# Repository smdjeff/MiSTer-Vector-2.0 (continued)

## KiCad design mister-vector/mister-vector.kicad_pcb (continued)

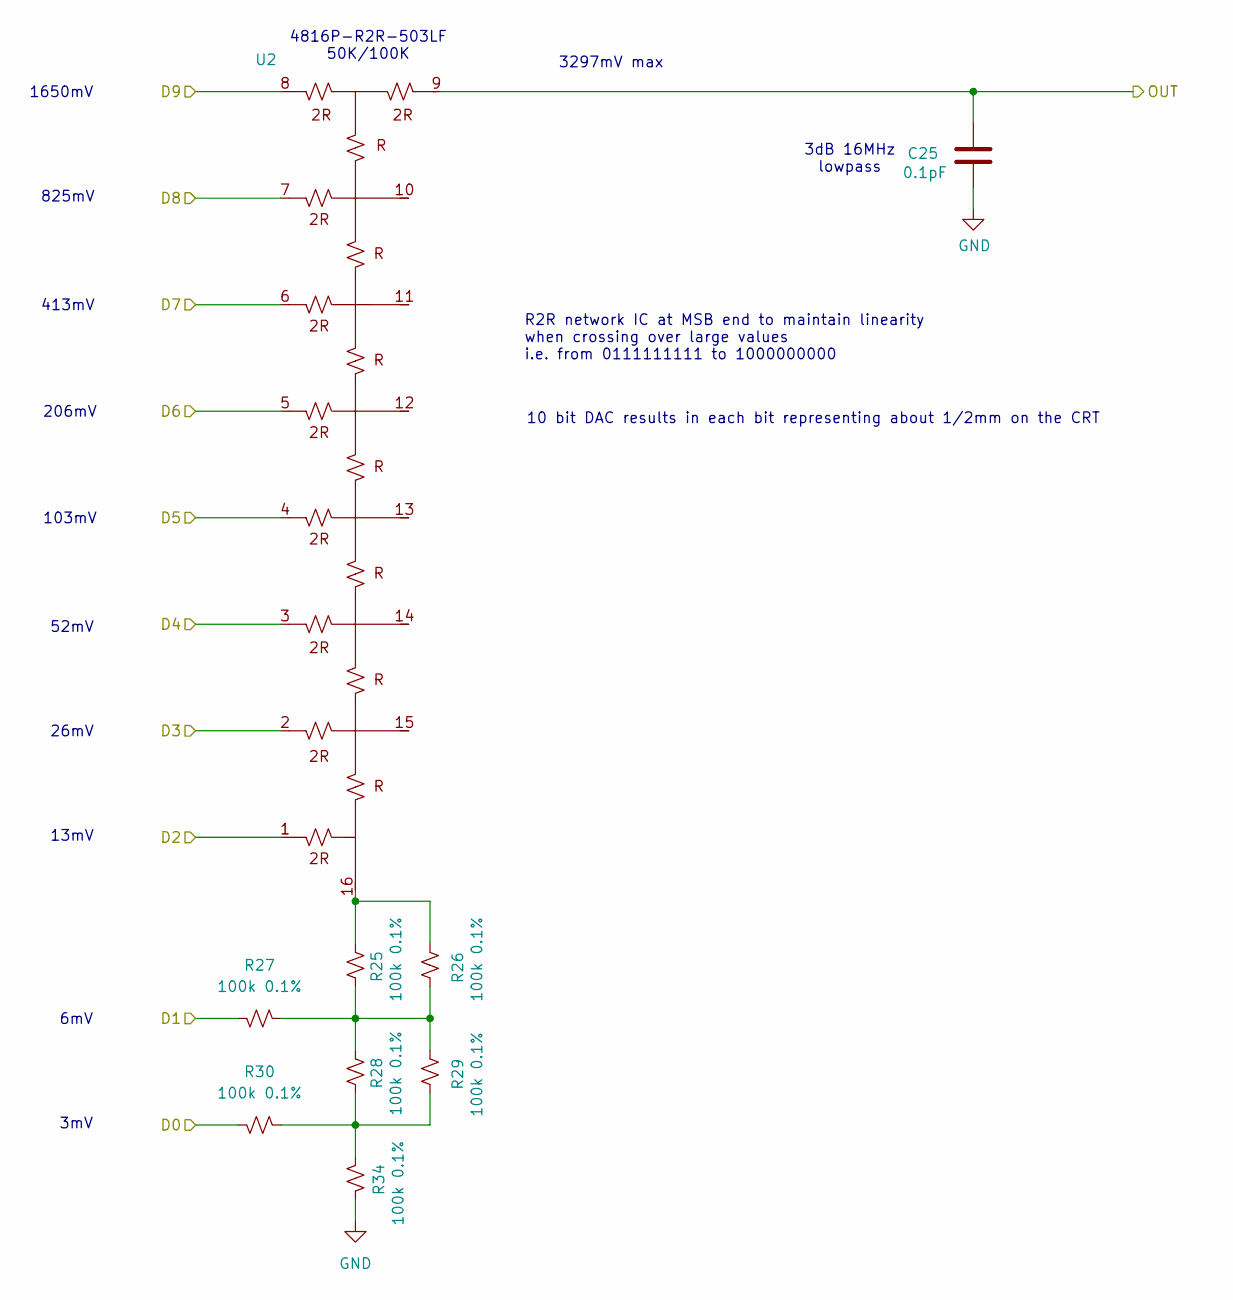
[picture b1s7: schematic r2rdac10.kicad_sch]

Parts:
C25: 0.1pF; C_0402_1005Metric; LCSC C5448807
R25, R26, R27, R28, R29, R30, R34: 100k 0.1%; R_0402_1005Metric; LCSC C852472
U2: 4816P-R2R-503LF; SOIC-16W_5.3x10.2mm_P1.27mm; LCSC C1518174

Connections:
/Vector Amplifiers/DAC_X: C25.2, U2.9; also elsewhere on the board
/Vector DACs/R2R_DAC_X/D0: R30.2; also elsewhere on the board
/Vector DACs/R2R_DAC_X/D1: R27.2; also elsewhere on the board
/Vector DACs/R2R_DAC_X/D2: U2.1; also elsewhere on the board
/Vector DACs/R2R_DAC_X/D3: U2.2; also elsewhere on the board
/Vector DACs/R2R_DAC_X/D4: U2.3; also elsewhere on the board
/Vector DACs/R2R_DAC_X/D5: U2.4; also elsewhere on the board
/Vector DACs/R2R_DAC_X/D6: U2.5; also elsewhere on the board
/Vector DACs/R2R_DAC_X/D7: U2.6; also elsewhere on the board
/Vector DACs/R2R_DAC_X/D8: U2.7; also elsewhere on the board
/Vector DACs/R2R_DAC_X/D9: U2.8; also elsewhere on the board
GND: C25.1, R34.2; also elsewhere on the board
unnamed: R25.1, R26.1, U2.16
unnamed: R25.2, R26.2, R27.1, R28.1, R29.1
unnamed: R28.2, R29.2, R30.1, R34.1

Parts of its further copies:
C26: 0.1pF; C_0402_1005Metric; LCSC C5448807
R35, R36, R37, R38, R39, R40, R44: 100k 0.1%; R_0402_1005Metric; LCSC C852472
U3: 4816P-R2R-503LF; SOIC-16W_5.3x10.2mm_P1.27mm; LCSC C1518174

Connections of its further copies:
/Vector Amplifiers/DAC_Y: C26.2, U3.9; also elsewhere on the board
/Vector DACs/R2R_DAC_Y/D0: R40.2; also elsewhere on the board
/Vector DACs/R2R_DAC_Y/D1: R37.2; also elsewhere on the board
/Vector DACs/R2R_DAC_Y/D2: U3.1; also elsewhere on the board
/Vector DACs/R2R_DAC_Y/D3: U3.2; also elsewhere on the board
/Vector DACs/R2R_DAC_Y/D4: U3.3; also elsewhere on the board
/Vector DACs/R2R_DAC_Y/D5: U3.4; also elsewhere on the board
/Vector DACs/R2R_DAC_Y/D6: U3.5; also elsewhere on the board
/Vector DACs/R2R_DAC_Y/D7: U3.6; also elsewhere on the board
/Vector DACs/R2R_DAC_Y/D8: U3.7; also elsewhere on the board
/Vector DACs/R2R_DAC_Y/D9: U3.8; also elsewhere on the board
GND: C26.1, R44.2; also elsewhere on the board
unnamed: R35.1, R36.1, U3.16
unnamed: R35.2, R36.2, R37.1, R38.1, R39.1
unnamed: R38.2, R39.2, R40.1, R44.1

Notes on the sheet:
103mV
R2R network IC at MSB end to maintain linearity when crossing over large values i.e. from 0111111111 to 1000000000
52mV
4816P-R2R-503LF 50K/100K
13mV
3297mV max
26mV
3mV
10 bit DAC results in each bit representing about 1/2mm on the CRT
6mV
1650mV
3dB 16MHz lowpass
413mV
206mV
825mV

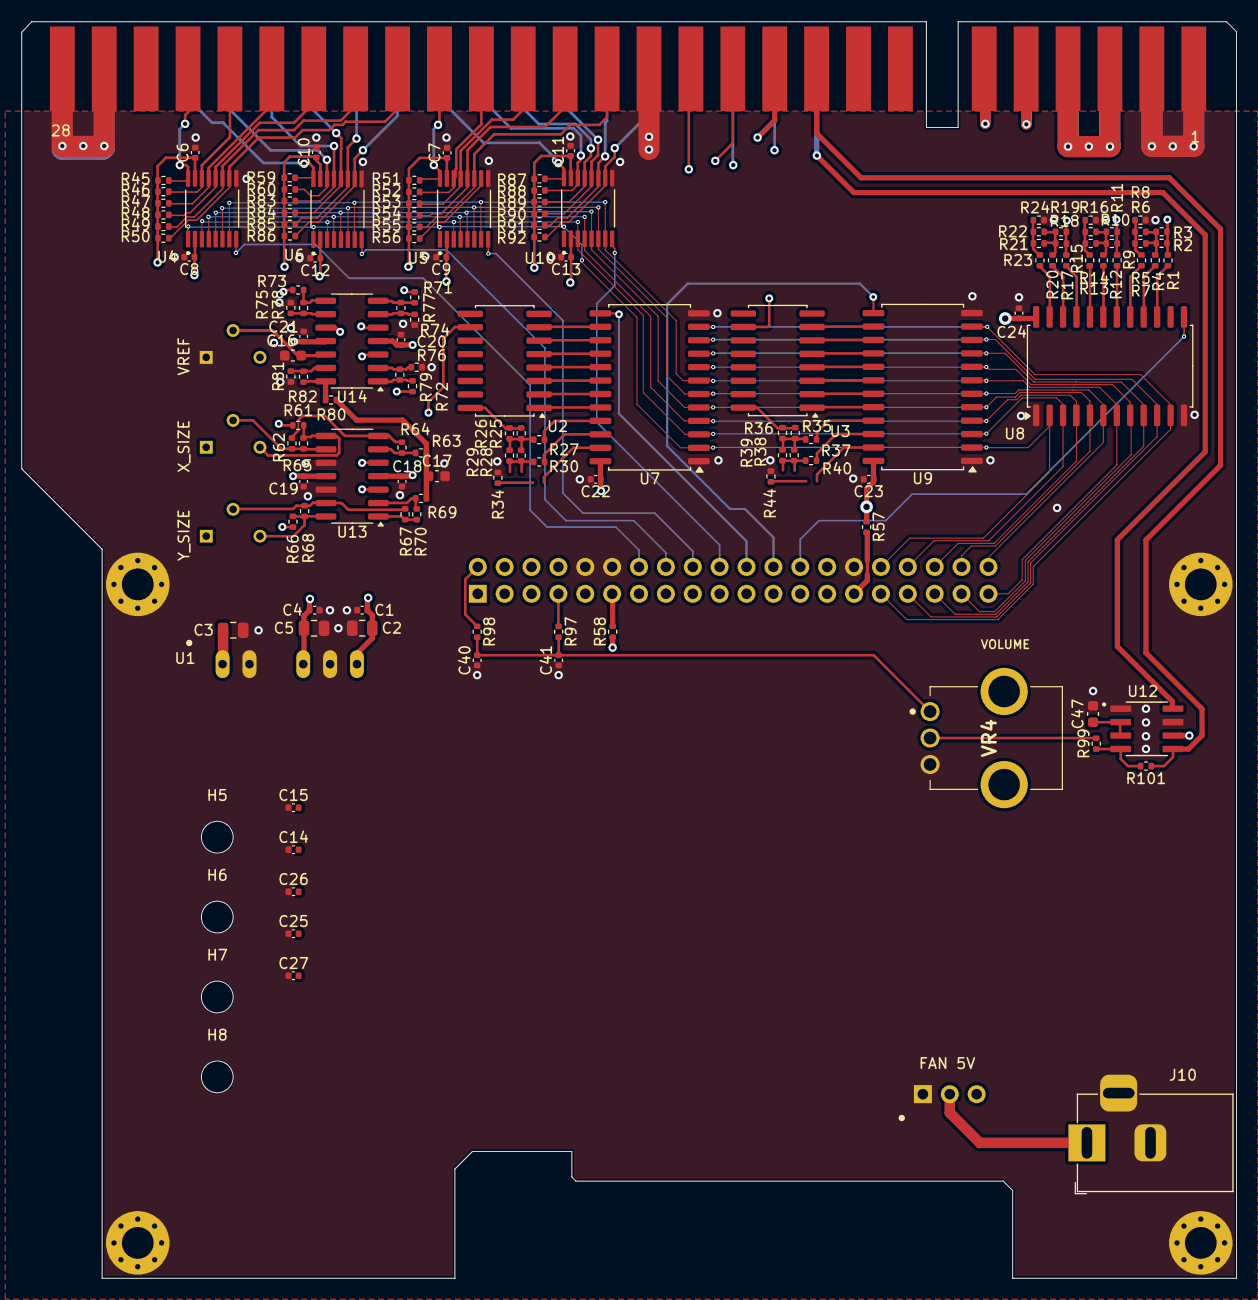
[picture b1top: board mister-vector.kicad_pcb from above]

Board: 4 copper layers, 114.8 x 118.8 mm, 149 parts (1 on the bottom side), 127 nets.

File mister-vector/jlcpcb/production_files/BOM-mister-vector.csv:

Comment,Designator,Footprint,LCSC,Quantity
75R,"R61,R62,R66,R67,R71,R72,R73,R80",R_0402_1005Metric,C114757,8
475R,"R97,R98",R_0402_1005Metric,C137975,2
1uF,"C16,C17,C47",C_0603_1608Metric,C15849,3
0,R57,R_0402_1005Metric,C17168,1
4.7uF,"C2,C3,C5",C_0805_2012Metric,C1779,3
100k,"R45,R46,R47,R48,R49,R50,R51,R52,R53,R54,R55,R56,R59,R60,R83,R84,R85,R86,R87,R88,R89,R90,R91,R92",R_0402_1005Metric,C25741,24
10K,"R63,R64,R65,R68,R69,R70,R74,R75,R76,R81",R_0402_1005Metric,C25744,10
20k,"R101,R99",R_0402_1005Metric,C25765,2
4K7,"R77,R78,R79,R82",R_0402_1005Metric,C25900,4
TL084HIDR,"U13,U14",SOIC-14_3.9x8.7mm_P1.27mm,C2878714,2
100nF,"C1,C10,C11,C12,C13,C18,C19,C20,C21,C22,C23,C24,C4,C6,C7,C8,C9",C_0402_1005Metric,C307331,17
TXB0106PWR,"U10,U4,U5,U6",SOP65P640X120-16N,C38253,4
20nF,C40,C_0402_1005Metric,C5448807,1
LM4871MX_NOPB,U12,SOIC127P599X175-8N,C7554,1
VREF,"VR1,VR2,VR3",TRIM_3362P-1-203LF,C81263,3
100k 0.1%,"R1,R10,R11,R12,R13,R14,R15,R16,R17,R18,R19,R2,R20,R21,R22,R23,R24,R25,R26,R27,R28,R29,R3,R30,R31,R32,R33,R34,R35,R36,R37,R38,R39,R4,R40,R41,R42,R43,R44,R5,R6,R7,R8,R9",R_0402_1005Metric,C852472,44

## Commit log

2025-05-30 convert to kicad
2025-05-31 relink refdegs
2025-06-03 reworking for r2r-dac and edge triggered buffers
2025-08-31 hierarchical schematic, add libraries
2025-08-31 update pcb screenshot
